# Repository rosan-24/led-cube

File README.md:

# 4x4x4 LED Cube (led-cube)

## About the project

A 4x4x4 LED cube (64 LEDs) powered by an ESP32 DEVKITV1. It runs from a single LiPo cell, with a charger and a boost converter on the board.

The main board is a two-layer PCB, 90.05 x 90.05 mm, 1.6 mm thick. The 64 LEDs and the cube frame are wired off the board.

This is a learning project. KiCad is new to me, so the design went through several rounds of fixes.

**Status:** schematic done, PCB routed, gerbers generated. Not yet built or tested.

---

## BOM

Prices are not filled in yet.

| sno | part | description | qty |
|---|---|---|---|
| 1 | ESP32 DEVKITV1 (30-pin) | Brain of the cube, runs the firmware | 1 |
| 2 | TP4056 charger module | Charges the LiPo cell over USB | 1 |
| 3 | 7Semi TPS61023 boost module | Boosts 3.7 V to 5 V for the ESP32 VIN | 1 |
| 4 | LiPo cell, 3.7 V | Powers the cube | 1 |
| 5 | Resistor, 220 ohm | Layer resistors R1 to R4 | 4 |
| 6 | Power switch SW1 | Turns the cube on and off (see Known issues) | 1 |
| 7 | 4-pin connector LI1, 4.8 mm pitch | Layer wires to the cube | 1 |
| 8 | Column pads L1 to L16 | Column wires to the cube (0.5 mm solder wire) | 16 |
| 9 | LED choose blue or red for better experince  | Cube LEDs, wired off the board | 64 |
| 10 | Enclosure | 3D printed, from `Enclosure.stl` | 1 |

---

## Project workflow

The full build log is in [JOURNAL.md](JOURNAL.md).

- **Nov 7:** Gathered the parts and started the schematic. Made the ESP32 DevKit symbol and the TPS61023 symbol, since neither was in the library.
- **Nov 11:** Finished the footprints for the ESP32, boost and charger, and reworked the schematic.
- **Nov 13:** Routed the wires with the right track width for each net, and used both copper layers.
- **Nov 16:** Designed the enclosure in Onshape.
- **Nov 18:** Routed the PCB and fixed the schematic and PCB design errors.
- **Nov 22:** Organized the LED layers, checked the connections, and added a hole for the ESP32 and text on the board.

---

## Schematic and PCB

**Schematic:** the ESP32 DevKit, TP4056 charger, TPS61023 boost, power switch, 4 layer resistors, the layer connector LI1 and 16 column pads.

**Power path:** LiPo cell to the TP4056 battery pads, then TP4056 OUT+ through SW1 to the boost input. The boost output (5 V) feeds the ESP32 VIN pin. All grounds are shared.

**PCB:**
- Two copper layers (F.Cu and B.Cu), 131 tracks,0 vias,0 copper pours.
- Track widths: 0.3 mm for LED layer and column nets, 0.5 mm for GND and VIN, 1.0 mm for the battery side.
- All 29 nets are fully routed.
- The gerbers in `Gerber.zip` match the current PCB.

---

## Pin map

Columns L1 to L16, one GPIO each, no resistor
Layers LI1 pins 1 to 4, each through a 220 ohm resistor
---

## Features

- 64 LEDs in four layers of 16 columns.
- Runs from a LiPo cell, with USB charging.
- Planned firmware

---
## How to build

- **Step 1:** Check you have all the parts from the BOM.
- **Step 2:** Then order the PCB from `Gerber.zip`.
- **Step 3:** Print the enclosure from `Enclosure.stl`.
https://github.com/rosan-24/led-cube/blob/main/CAD/Assembly%201.step
- **Step 4:** Solder the parts, connect the battery and the cube wiring, and check every column and layer by hand.
- **Step 5:** Flash the firmware once it's added to the repo.

---

## Contributors

- [@rosan-24](https://github.com/rosan-24)

---

## Resources

- [JOURNAL.md](JOURNAL.md): full build log, November 7 to 22, 2026.

---

## Special credits

- The build log is written for Hack Club Fabricate.

---

## License
.--. .-. .. ...
    ~rosh

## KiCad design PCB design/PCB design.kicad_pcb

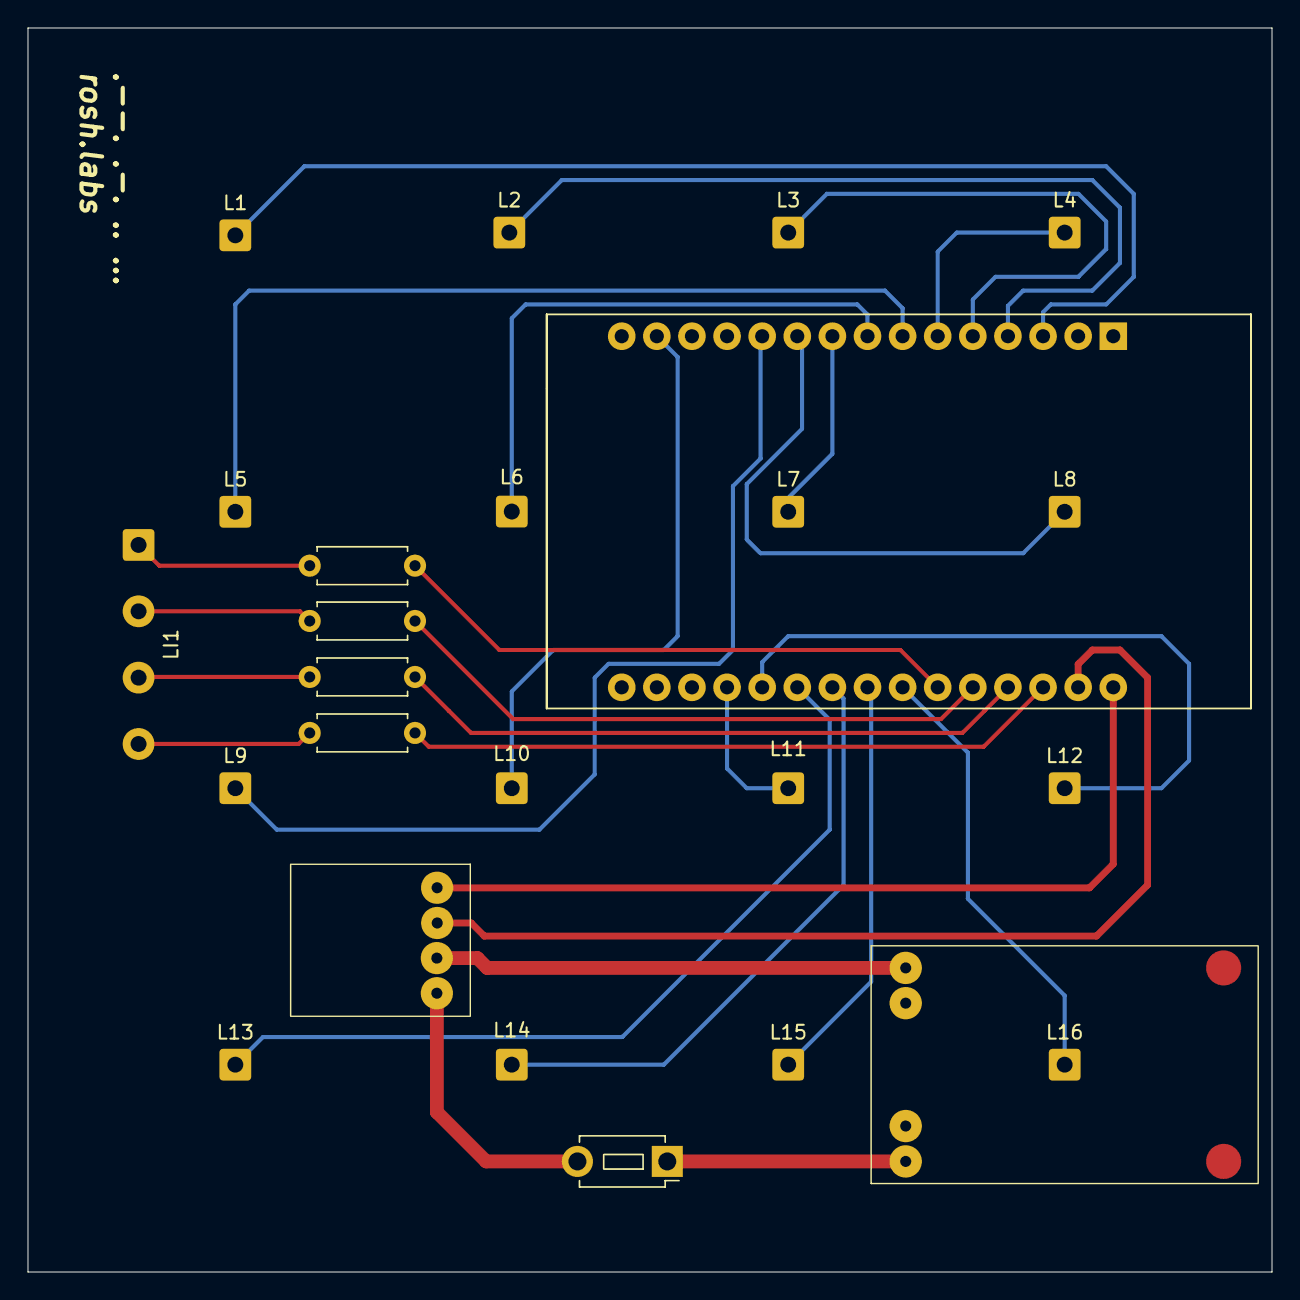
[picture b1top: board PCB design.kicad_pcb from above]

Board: 2 copper layers, 90.0 x 90.0 mm, 25 parts (0 on the bottom side), 29 nets.

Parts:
.1: TP4056
ESP32: MODULE_ESP32_DEVKIT_V1
L1, L2, L3, L4, L5, L6, L7, L8, L9, L10, L11, L12, L13, L14, L15, L16: Conn_01x01; SolderWire-0.5sqmm_1x01_D0.9mm_OD2.3mm
LI1: Conn_01x04; SolderWire-0.5sqmm_1x04_P4.8mm_D0.9mm_OD2.3mm
R1, R2, R3, R4: 220; R_Axial_DIN0207_L6.3mm_D2.5mm_P7.62mm_Horizontal
SW1: SW_SPST; SW_PUSH_1P1T_6x3.5mm_H5.0_APEM_MJTP1250
boost: 7semi tps61023; 7Semi Tps61023

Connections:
unnamed: .1.4 (out+), SW1.1 (A)
unnamed: .1.1 (out-), boost.3 (GND)
unnamed: ESP32.4 (D02), L2.1 (Pin_1_1)
unnamed: ESP32.5 (D04), L3.1 (Pin_1_1)
unnamed: ESP32.8 (D05), L6.1 (Pin_1_1)
unnamed: ESP32.27 (D12), R3.2
unnamed: ESP32.28 (D13), R4.2
unnamed: ESP32.26 (D14), R2.2
unnamed: ESP32.3 (D15), L1.1 (Pin_1_1)
unnamed: ESP32.9 (D18), L7.1 (Pin_1_1)
unnamed: ESP32.10 (D19), L8.1 (Pin_1_1)
unnamed: ESP32.11 (D21), L9.1 (Pin_1_1)
unnamed: ESP32.14 (D22), L10.1 (Pin_1_1)
unnamed: ESP32.23 (D25), L15.1 (Pin_1_1)
unnamed: ESP32.24 (D26), L16.1 (Pin_1_1)
unnamed: ESP32.25 (D27), R1.2
unnamed: ESP32.21 (D32), L13.1 (Pin_1_1)
unnamed: ESP32.22 (D33), L14.1 (Pin_1_1)
unnamed: ESP32.19 (D34), L11.1 (Pin_1_1)
unnamed: ESP32.20 (D35), L12.1 (Pin_1_1)
unnamed: ESP32.29 (GND), boost.2 (GND)
unnamed: ESP32.6 (RX2), L4.1 (Pin_1_1)
unnamed: ESP32.7 (TX2), L5.1 (Pin_1_1)
unnamed: ESP32.30 (VIN), boost.1 (5V)
unnamed: LI1.1, R1.1
unnamed: LI1.2, R2.1
unnamed: LI1.3, R3.1
unnamed: LI1.4, R4.1
unnamed: SW1.2 (B), boost.4 (VIN)
